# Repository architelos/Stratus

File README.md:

# Stratus

A custom, open source yet practical drone stack.\
Open sourced in the hope that it could serve as a stepping stone in someone else's journey!

## ESC - Jett

**Current revision:** 3\
**Status:** Testing

### Specs

|                    |                                                    |
| ------------------ | -------------------------------------------------- |
| MCU                | STM32G071K(B/8)U(3/6)                              |
| Gate driver        | DRV8300DRGER                                       |
| Input              | 3S to 5S LiPo                                      |
| Continuous current | 25A, 30A peaks                                     |
| Current sensing    | High side hall effect sensor (ACS711)              |
| Firmware           | AM32                                               |

### Description

Built from the ground up to understand what is happening inside an ESC, rather than treating it as a black box. Jett uses industry standard AM32, and has hardware designed around being able to inspect, modify, and learn from the system.

**Power tree:** `VBAT → 10V buck (driving FETs) → 3.3V low-noise LDO`

## Kite (FC)

**Current revision:** 1\
**Status:** Waiting for Jett

### Specs

|                    |                                                    |
| ------------------ | -------------------------------------------------- |
| MCU                | RP2354A                                            |
| IMU                | LSM6DSK320X                                        |
| Input              | 3S to 4S LiPo                                      |
| BECs               | 5V → VTX + Camera; 3V3 → MCU + IMU                 |
| Storage            | MicroSD                                            |
| Firmware           | Betaflight                                         |

The flight controller completes the Stratus stack, with the same focus on practical hardware and understanding the underlying system.

## Acknowledgements <3

Thank you to:
- **AlkaMotors**, **brushlesspower** for the endless patience and willingness to share experience.
- **anticitizen**, **Diamond Master** for design reviews and contributions.

This project would not have been possible without you!

## License

CERN-OHL-S-2.0, see [LICENSE](LICENSE).

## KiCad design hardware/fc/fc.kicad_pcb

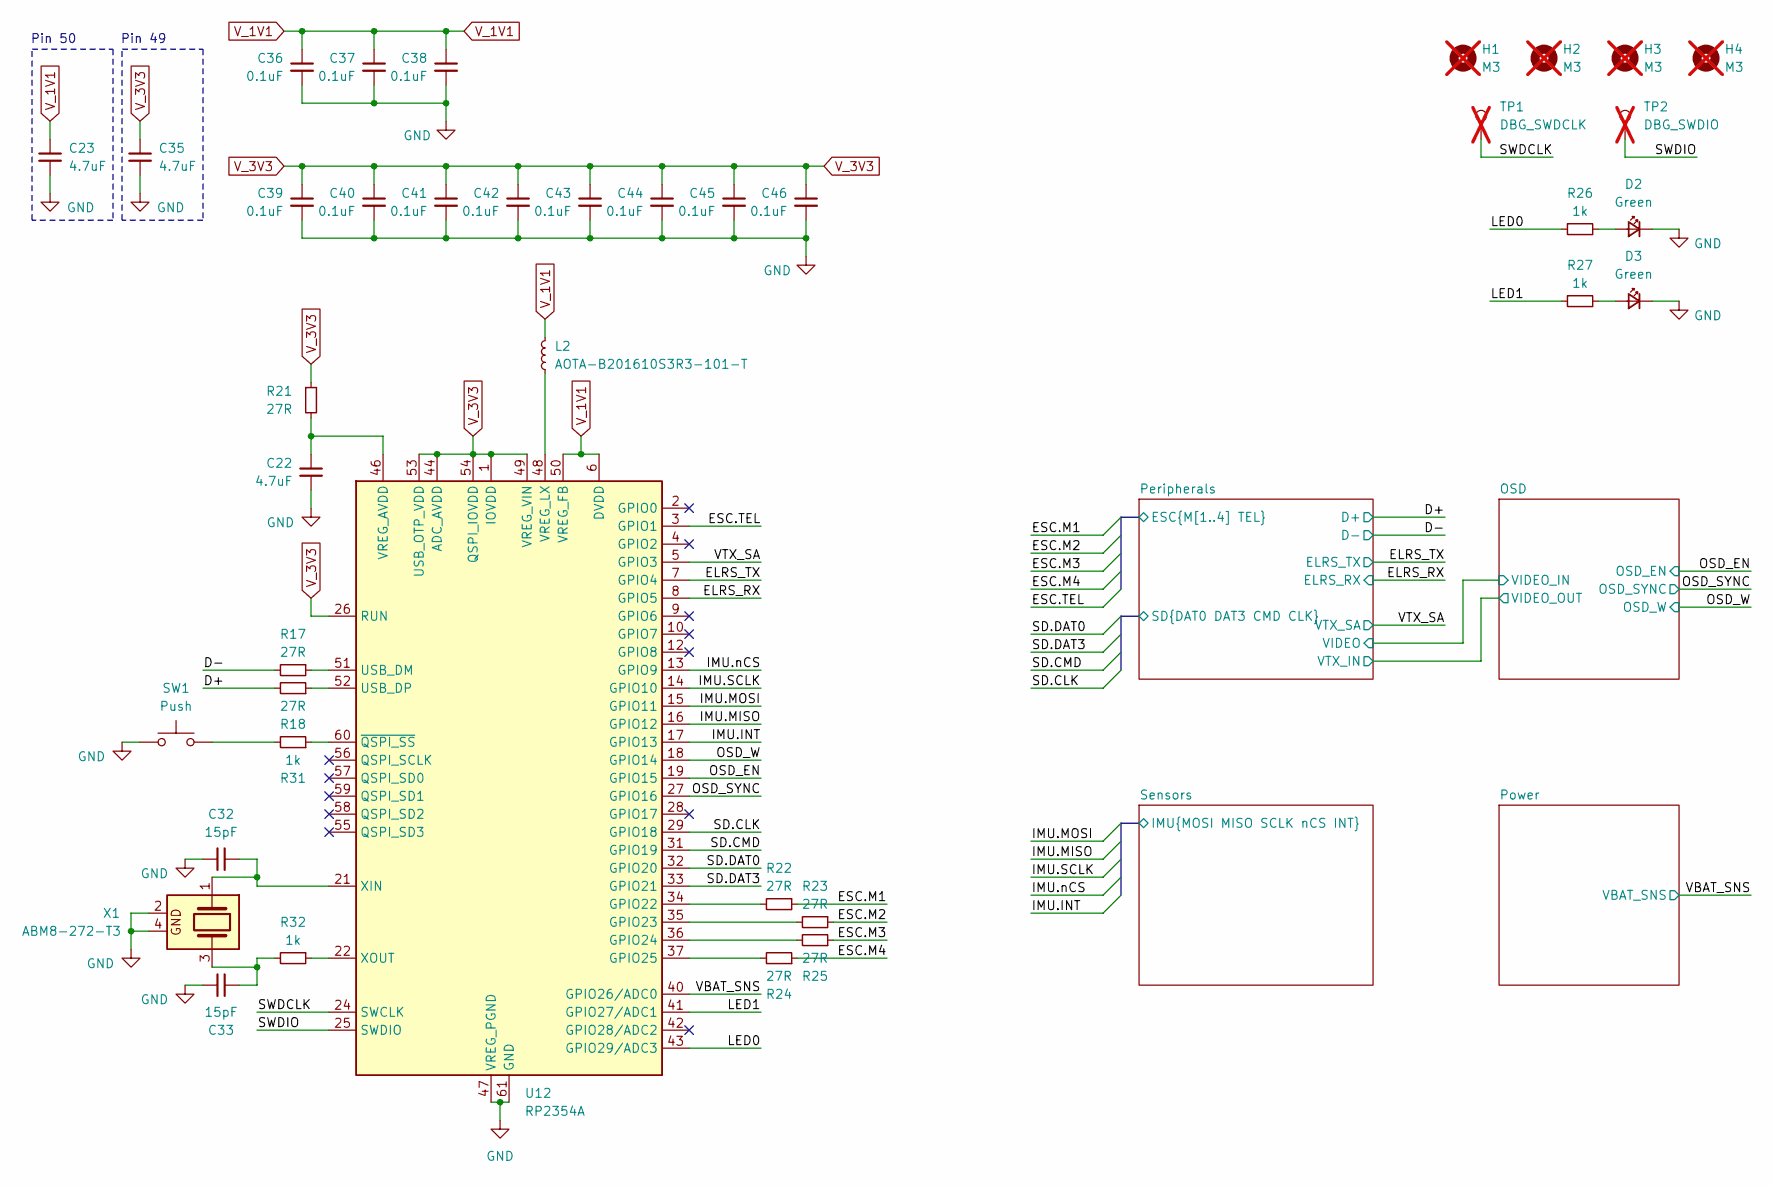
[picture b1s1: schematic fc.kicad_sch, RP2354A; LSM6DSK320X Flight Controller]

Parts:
C22, C23, C35: 4.7uF; C_0402; MPN TDK105CBJ475MV-F; LCSC# C22385335
C32, C33: 15pF; C_0402; MPN CGA2B2C0G1H150JT0Y0F; LCSC# C338103
C36, C37, C38, C39, C40, C41, C42, C43, C44, C45, C46: 0.1uF; C_0402; MPN CGA2B3X7R1V104KT0Y0F; LCSC# C343047
D2, D3: Green; LED_0603_1608Metric; MPN VLMTG1400-GS08; LCSC# C3000897
H1, H2, H3, H4: M3; Mount_M3_K0.5; not fitted
L2: AOTA-B201610S3R3-101-T; L_0806; MPN AOTA-B201610S3R3-101-T; LCSC# C42411119
R17, R18, R21, R22, R23, R24, R25: 27R; R_0402; MPN AC0402FR-0727RL; LCSC# C226392
R26, R27, R31, R32: 1k; R_0402; MPN RC0402FR-071KL; LCSC# C106235
SW1: Push; Push_2x3; MPN EVPAWED40; LCSC# C2858607
TP1: DBG_SWDCLK; Debug_Pad_D1; not fitted
TP2: DBG_SWDIO; Debug_Pad_D1; not fitted
U12: RP2354A; MPN RP2354A; LCSC# C41378174
X1: ABM8-272-T3; Crystal_4P_3.2x2.5mm; MPN ABM8-272-T3; LCSC# C20625731

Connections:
/D+: R18.2; also elsewhere on the board
/D-: R17.2; also elsewhere on the board
/ELRS_RX: U12.8 (GPIO5); also elsewhere on the board
/ELRS_TX: U12.7 (GPIO4); also elsewhere on the board
/LED0: R26.1, U12.43 (GPIO29/ADC3)
/LED1: R27.1, U12.41 (GPIO27/ADC1)
/OSD_EN: U12.19 (GPIO15); also elsewhere on the board
/OSD_SYNC: U12.27 (GPIO16); also elsewhere on the board
/OSD_W: U12.18 (GPIO14); also elsewhere on the board
/Peripherals/ESC.M1: R22.1; also elsewhere on the board
/Peripherals/ESC.M2: R23.1; also elsewhere on the board
/Peripherals/ESC.M3: R25.1; also elsewhere on the board
/Peripherals/ESC.M4: R24.1; also elsewhere on the board
/Peripherals/ESC.TEL: U12.3 (GPIO1); also elsewhere on the board
/Peripherals/SD.CLK: U12.29 (GPIO18); also elsewhere on the board
/Peripherals/SD.CMD: U12.31 (GPIO19); also elsewhere on the board
/Peripherals/SD.DAT0: U12.32 (GPIO20); also elsewhere on the board
/Peripherals/SD.DAT3: U12.33 (GPIO21); also elsewhere on the board
/SWDCLK: TP1.1 (1_1), U12.24 (SWCLK)
/SWDIO: TP2.1 (1_1), U12.25 (SWDIO)
/Sensors/IMU.INT: U12.17 (GPIO13); also elsewhere on the board
/Sensors/IMU.MISO: U12.16 (GPIO12); also elsewhere on the board
/Sensors/IMU.MOSI: U12.15 (GPIO11); also elsewhere on the board
/Sensors/IMU.SCLK: U12.14 (GPIO10); also elsewhere on the board
/Sensors/IMU.nCS: U12.13 (GPIO9); also elsewhere on the board
/VBAT_SNS: U12.40 (GPIO26/ADC0); also elsewhere on the board
/VTX_SA: U12.5 (GPIO3); also elsewhere on the board
GND: C22.2, C23.2, C32.2, C33.2, C35.2, C36.2, C37.2, C38.2, C39.2, C40.2, C41.2, C42.2, C43.2, C44.2, C45.2, C46.2, D2.1 (K), D3.1 (K), SW1.1, U12.47 (VREG_PGND), U12.61 (GND), X1.2, X1.4; also elsewhere on the board
unnamed: C33.1, R32.2, X1.3
unnamed: D2.2 (A), R26.2
unnamed: D3.2 (A), R27.2
unnamed: R31.2, SW1.2
unnamed: R22.2, U12.34 (GPIO22)
unnamed: R23.2, U12.35 (GPIO23)
unnamed: R25.2, U12.36 (GPIO24)
unnamed: R24.2, U12.37 (GPIO25)
unnamed: R17.1, U12.51 (USB_DM)
unnamed: R18.1, U12.52 (USB_DP)
unnamed: C22.1, R21.2, U12.46 (VREG_AVDD)
unnamed: L2.1, U12.48 (VREG_LX)
unnamed: C32.1, U12.21 (XIN), X1.1
unnamed: R32.1, U12.22 (XOUT)
unnamed: R31.1, U12.60 (~QSPI_SS)
V_1V1: C23.1, C36.1, C37.1, C38.1, L2.2, U12.6 (DVDD), U12.23 (DVDD), U12.39 (DVDD), U12.50 (VREG_FB)
V_3V3: C35.1, C39.1, C40.1, C41.1, C42.1, C43.1, C44.1, C45.1, C46.1, R21.1, U12.1 (IOVDD), U12.11 (IOVDD), U12.20 (IOVDD), U12.26 (RUN), U12.30 (IOVDD), U12.38 (IOVDD), U12.44 (ADC_AVDD), U12.45 (IOVDD), U12.49 (VREG_VIN), U12.53 (USB_OTP_VDD), U12.54 (QSPI_IOVDD); also elsewhere on the board

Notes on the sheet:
Pin 50
Pin 49

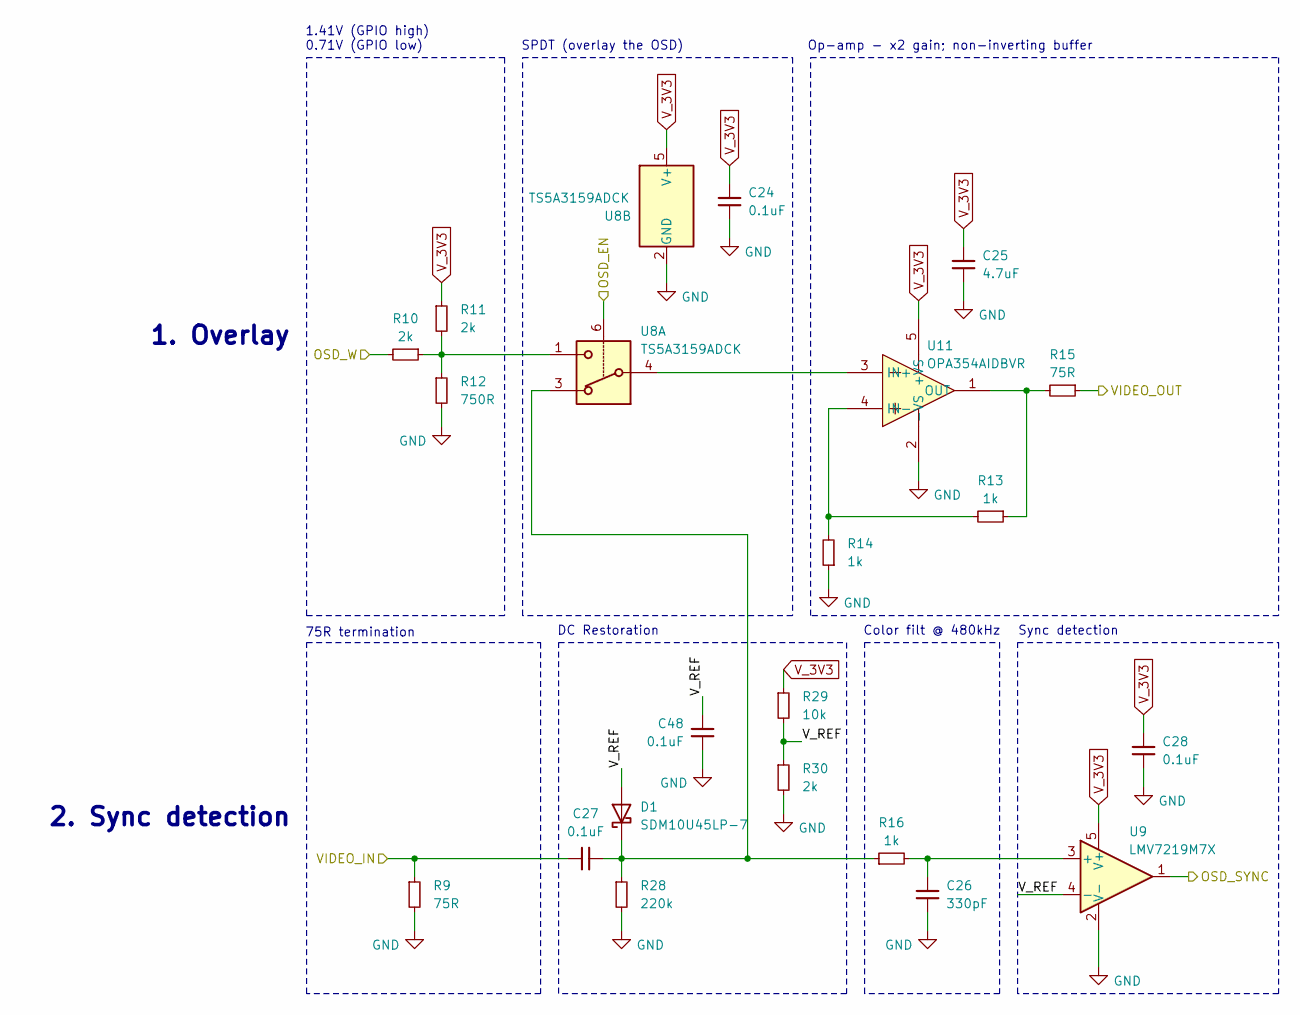
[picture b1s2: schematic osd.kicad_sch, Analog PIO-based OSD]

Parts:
C24, C27, C28, C48: 0.1uF; C_0402; MPN CGA2B3X7R1V104KT0Y0F; LCSC# C343047
C25: 4.7uF; C_0402; MPN TDK105CBJ475MV-F; LCSC# C22385335
C26: 330pF; C_0402; MPN GRM1555C1H331JA01D; LCSC# C76965
D1: SDM10U45LP-7; D_0402; MPN SDM10U45LP-7; LCSC# C78151
R9, R15: 75R; R_0402; MPN RC0402FR-0775RL; LCSC# C114757
R10, R11, R30: 2k; R_0402; MPN RC0402FR-072KL; LCSC# C60488
R12: 750R; R_0402; MPN RC0402FR-07750RL; LCSC# C137936
R13, R14, R16: 1k; R_0402; MPN RC0402FR-071KL; LCSC# C106235
R28: 220k; R_0402; MPN AC0402FR-07220KL; LCSC# C144780
R29: 10k; R_0402; MPN AC0402FR-0710KL; LCSC# C144807
U8: TS5A3159ADCK; MPN TS5A3159ADCK; LCSC# C475493
U9: LMV7219M7X; LMV7219M7X_NOPB; MPN LMV7219M7X; LCSC# C544337
U11: OPA354AIDBVR; MPN OPA354AIDBVR; LCSC# C36384

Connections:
/OSD/VIDEO_IN: C27.2, R9.1; also elsewhere on the board
/OSD/VIDEO_OUT: R15.1; also elsewhere on the board
/OSD/V_REF: C48.2, D1.2 (A), R29.2, R30.1, U9.4 (-)
/OSD_EN: U8.6; also elsewhere on the board
/OSD_SYNC: U9.1; also elsewhere on the board
/OSD_W: R10.2; also elsewhere on the board
GND: C24.2, C25.2, C26.2, C28.2, C48.1, R9.2, R12.2, R14.1, R28.2, R30.2, U8.2 (GND), U9.2 (V-), U11.2 (-VS); also elsewhere on the board
unnamed: C27.1, D1.1 (K), R16.1, R28.1, U8.3
unnamed: R10.1, R11.2, R12.1, U8.1
unnamed: C26.1, R16.2, U9.3 (+)
unnamed: U8.4, U11.3 (IN+)
unnamed: R13.2, R14.2, U11.4 (IN-)
unnamed: R13.1, R15.2, U11.1 (OUT)
V_3V3: C24.1, C25.1, C28.1, R11.1, R29.1, U8.5 (V+), U9.5 (V+), U11.5 (+VS); also elsewhere on the board

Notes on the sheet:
75R termination
Op-amp - x2 gain; non-inverting buffer
2. Sync detection
1.41V (GPIO high) 0.71V (GPIO low)
Color filt @ 480kHz
Sync detection
DC Restoration
SPDT (overlay the OSD)
1. Overlay

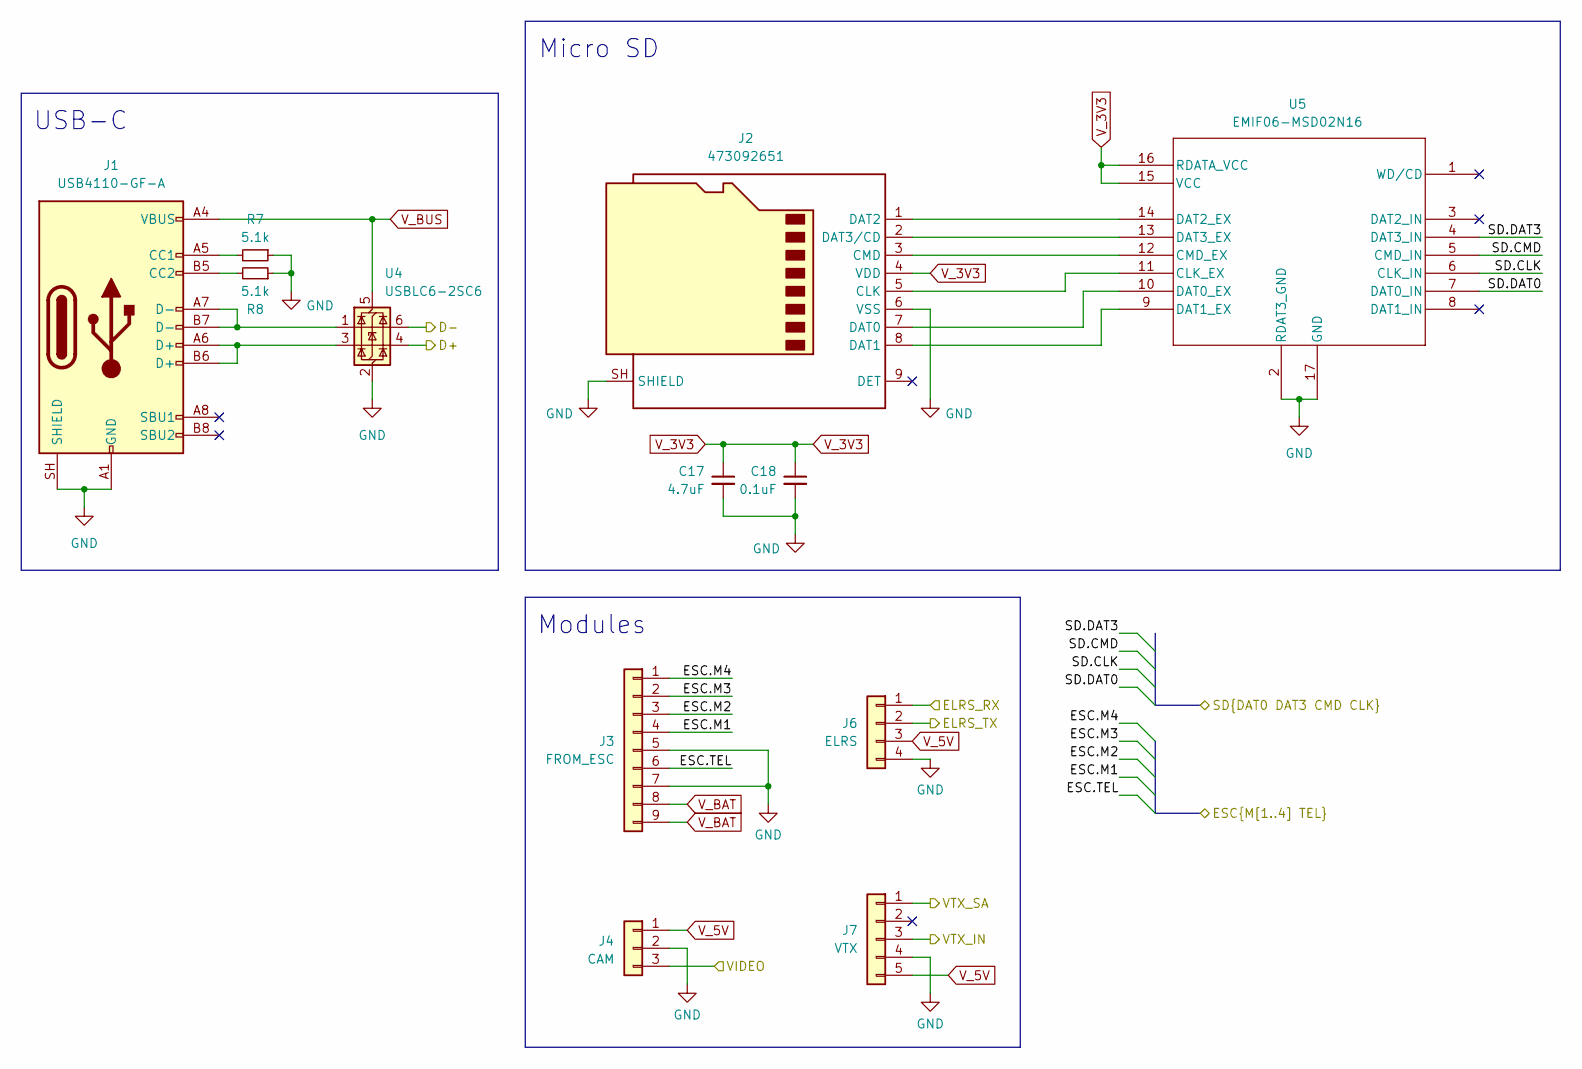
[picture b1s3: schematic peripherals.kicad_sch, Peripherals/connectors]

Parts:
C17: 4.7uF; C_0402; MPN TDK105CBJ475MV-F; LCSC# C22385335
C18: 0.1uF; C_0402; MPN CGA2B3X7R1V104KT0Y0F; LCSC# C343047
J1: USB4110-GF-A; USB_C_Receptacle_GCT_USB4110; MPN USB4110-GF-A; LCSC# C5143397
J2: 473092651; 0473092651; MPN 473092651; LCSC# C587826
J3: FROM_ESC; JST_SH_SM09B-SRSS-TB_1x09-1MP_P1.00mm_Horizontal; MPN SM09B-SRSS-TB(LF)(SN); LCSC# C160408
J4: CAM; JST_SH_SM03B-SRSS-TB_1x03-1MP_P1.00mm_Horizontal; MPN SM03B-SRSS-TB(LF)(SN); LCSC# C160403
J6: ELRS; JST_SH_SM04B-SRSS-TB_1x04-1MP_P1.00mm_Horizontal; MPN SM04B-SRSS-TB(LF)(SN); LCSC# C160404
J7: VTX; JST_SH_SM05B-SRSS-TB_1x05-1MP_P1.00mm_Horizontal; MPN SM05B-SRSS-TB(LF)(SN); LCSC# C136657
R7, R8: 5.1k; R_0402; MPN RC0402FR-075K1L; LCSC# C105872
U4: USBLC6-2SC6; MPN USBLC6-2SC6; LCSC# C7519
U5: EMIF06-MSD02N16; MPN EMIF06-MSD02N16; LCSC# C5267594

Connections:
/D+: U4.4 (I/O2); also elsewhere on the board
/D-: U4.6 (I/O1); also elsewhere on the board
/ELRS_RX: J6.1; also elsewhere on the board
/ELRS_TX: J6.2; also elsewhere on the board
/OSD/VIDEO_IN: J4.3; also elsewhere on the board
/OSD/VIDEO_OUT: J7.3; also elsewhere on the board
/Peripherals/ESC.M1: J3.4; also elsewhere on the board
/Peripherals/ESC.M2: J3.3; also elsewhere on the board
/Peripherals/ESC.M3: J3.2; also elsewhere on the board
/Peripherals/ESC.M4: J3.1; also elsewhere on the board
/Peripherals/ESC.TEL: J3.6; also elsewhere on the board
/Peripherals/SD.CLK: U5.6 (CLK_IN); also elsewhere on the board
/Peripherals/SD.CMD: U5.5 (CMD_IN); also elsewhere on the board
/Peripherals/SD.DAT0: U5.7 (DAT0_IN); also elsewhere on the board
/Peripherals/SD.DAT3: U5.4 (DAT3_IN); also elsewhere on the board
/VTX_SA: J7.1; also elsewhere on the board
GND: C17.2, C18.2, J1.A1 (GND), J1.A12 (GND), J1.B1 (GND), J1.B12 (GND), J1.SH (SHIELD), J2.6 (VSS), J2.SH (SHIELD), J3.5, J3.7, J4.2, J6.4, J7.4, R7.1, R8.1, U4.2 (GND), U5.2 (RDAT3_GND), U5.17 (GND); also elsewhere on the board
unnamed: J1.A5 (CC1), R7.2
unnamed: J1.B5 (CC2), R8.2
unnamed: J1.A6 (D+), J1.B6 (D+), U4.3 (I/O2)
unnamed: J1.A7 (D-), J1.B7 (D-), U4.1 (I/O1)
unnamed: J2.5 (CLK), U5.11 (CLK_EX)
unnamed: J2.3 (CMD), U5.12 (CMD_EX)
unnamed: J2.7 (DAT0), U5.10 (DAT0_EX)
unnamed: J2.8 (DAT1), U5.9 (DAT1_EX)
unnamed: J2.1 (DAT2), U5.14 (DAT2_EX)
unnamed: J2.2 (DAT3/CD), U5.13 (DAT3_EX)
V_3V3: C17.1, C18.1, J2.4 (VDD), U5.15 (VCC), U5.16 (RDATA_VCC); also elsewhere on the board
V_5V: J4.1, J6.3, J7.5; also elsewhere on the board
V_BAT: J3.8, J3.9; also elsewhere on the board
V_BUS: J1.A4 (VBUS), J1.A9 (VBUS), J1.B4 (VBUS), J1.B9 (VBUS), U4.5 (VBUS); also elsewhere on the board

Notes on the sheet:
USB-C
Micro SD
Modules

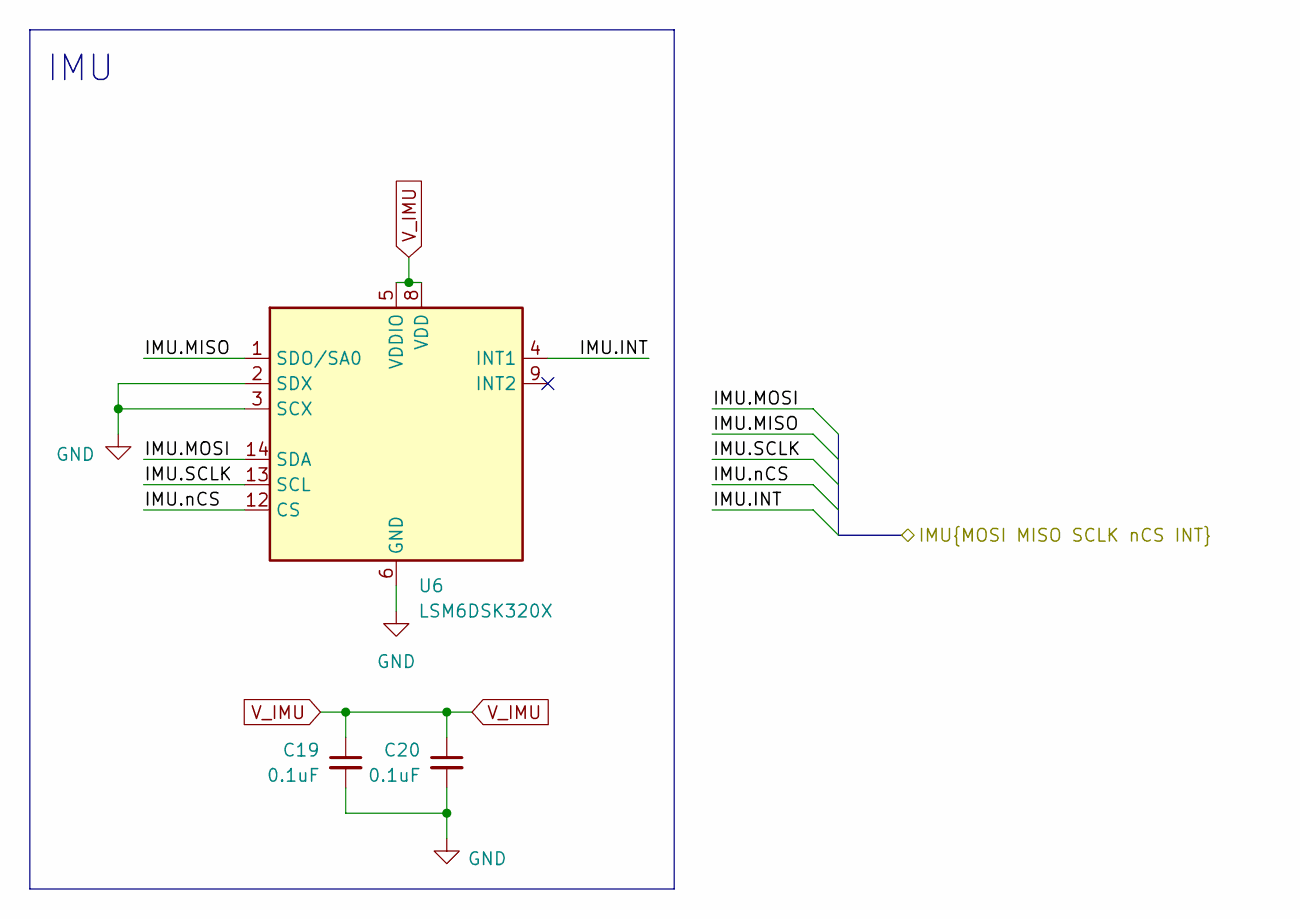
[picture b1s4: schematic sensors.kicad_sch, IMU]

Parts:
C19, C20: 0.1uF; C_0402; MPN CGA2B3X7R1V104KT0Y0F; LCSC# C343047
U6: LSM6DSK320X; MPN LSM6DSK320XTR; LCSC# C53025794

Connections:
/Sensors/IMU.INT: U6.4 (INT1); also elsewhere on the board
/Sensors/IMU.MISO: U6.1 (SDO/SA0); also elsewhere on the board
/Sensors/IMU.MOSI: U6.14 (SDA); also elsewhere on the board
/Sensors/IMU.SCLK: U6.13 (SCL); also elsewhere on the board
/Sensors/IMU.nCS: U6.12 (CS); also elsewhere on the board
GND: C19.2, C20.2, U6.2 (SDX), U6.3 (SCX), U6.6 (GND), U6.7 (GND); also elsewhere on the board
V_IMU: C19.1, C20.1, U6.5 (VDDIO), U6.8 (VDD); also elsewhere on the board

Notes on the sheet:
IMU

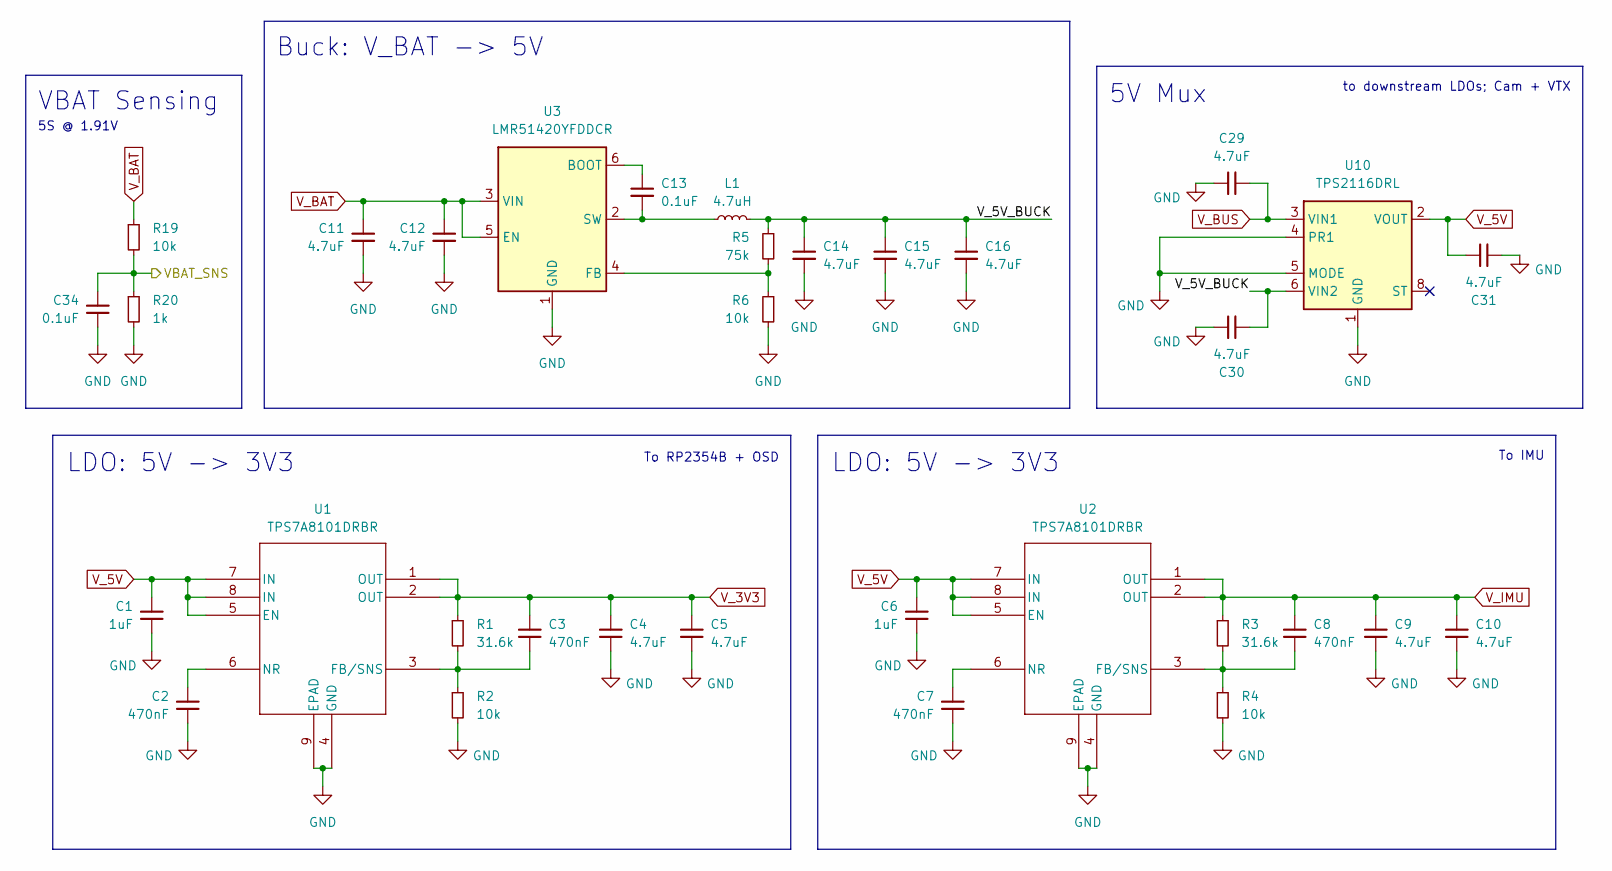
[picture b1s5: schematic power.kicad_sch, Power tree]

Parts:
C1, C6: 1uF; C_0402; MPN GRM155R6YA105KE11J; LCSC# C3835721
C2, C3, C7, C8: 470nF; C_0402; MPN CL05A474KA5NNNC; LCSC# C92361
C4, C5, C9, C10, C14, C15, C16, C29, C30, C31: 4.7uF; C_0402; MPN TDK105CBJ475MV-F; LCSC# C22385335
C11, C12: 4.7uF; C_0603_1608Metric; MPN CL10A475KL8NRNC; LCSC# C307467
C13, C34: 0.1uF; C_0402; MPN CGA2B3X7R1V104KT0Y0F; LCSC# C343047
L1: 4.7uH; L_1210_3225Metric; MPN BCL322520RT-4R7M-D; LCSC# C3224690
R1, R3: 31.6k; R_0402; MPN AC0402FR-0731K6L; LCSC# C226989
R2, R4, R6, R19: 10k; R_0402; MPN AC0402FR-0710KL; LCSC# C144807
R5: 75k; R_0402; MPN RC0402FR-0775KL; LCSC# C137935
R20: 1k; R_0402; MPN RC0402FR-071KL; LCSC# C106235
U1, U2: TPS7A8101DRBR; MPN TPS7A8101DRBR; LCSC# C465730
U3: LMR51420YFDDCR; MPN LMR51420YFDDCR; LCSC# C7296200
U10: TPS2116DRL; MPN TPS2116DRLR; LCSC# C3235557

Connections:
/Power/V_5V_BUCK: C14.1, C15.1, C16.1, C30.1, L1.2, R5.1, U10.6 (VIN2)
/VBAT_SNS: C34.1, R19.2, R20.1; also elsewhere on the board
GND: C1.2, C2.2, C4.2, C5.2, C6.2, C7.2, C9.2, C10.2, C11.2, C12.2, C14.2, C15.2, C16.2, C29.2, C30.2, C31.2, C34.2, R2.2, R4.2, R6.2, R20.2, U1.4 (GND), U1.9 (EPAD), U2.4 (GND), U2.9 (EPAD), U3.1 (GND), U10.1 (GND), U10.4 (PR1), U10.5 (MODE); also elsewhere on the board
unnamed: C3.2, R1.2, R2.1, U1.3 (FB/SNS)
unnamed: C2.1, U1.6 (NR)
unnamed: C8.2, R3.2, R4.1, U2.3 (FB/SNS)
unnamed: C7.1, U2.6 (NR)
unnamed: C13.1, U3.6 (BOOT)
unnamed: R5.2, R6.1, U3.4 (FB)
unnamed: C13.2, L1.1, U3.2 (SW)
V_3V3: C3.1, C4.1, C5.1, R1.1, U1.1 (OUT), U1.2 (OUT); also elsewhere on the board
V_5V: C1.1, C6.1, C31.1, U1.5 (EN), U1.7 (IN), U1.8 (IN), U2.5 (EN), U2.7 (IN), U2.8 (IN), U10.2 (VOUT), U10.7 (VOUT); also elsewhere on the board
V_BAT: C11.1, C12.1, R19.1, U3.3 (VIN), U3.5 (EN); also elsewhere on the board
V_BUS: C29.1, U10.3 (VIN1); also elsewhere on the board
V_IMU: C8.1, C9.1, C10.1, R3.1, U2.1 (OUT), U2.2 (OUT); also elsewhere on the board

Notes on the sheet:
VBAT Sensing
To RP2354B + OSD
LDO: 5V -> 3V3
5V Mux
To IMU
Buck: V_BAT -> 5V
5S @ 1.91V
to downstream LDOs; Cam + VTX

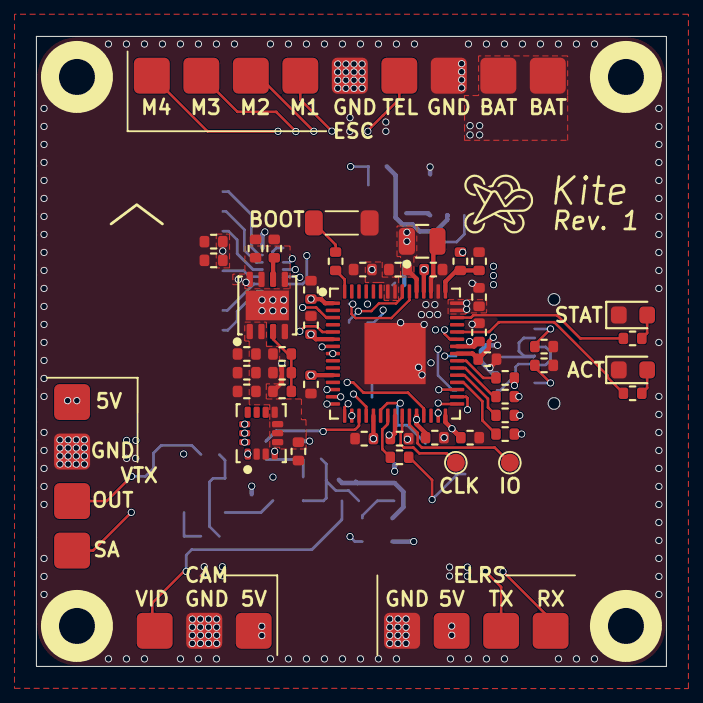
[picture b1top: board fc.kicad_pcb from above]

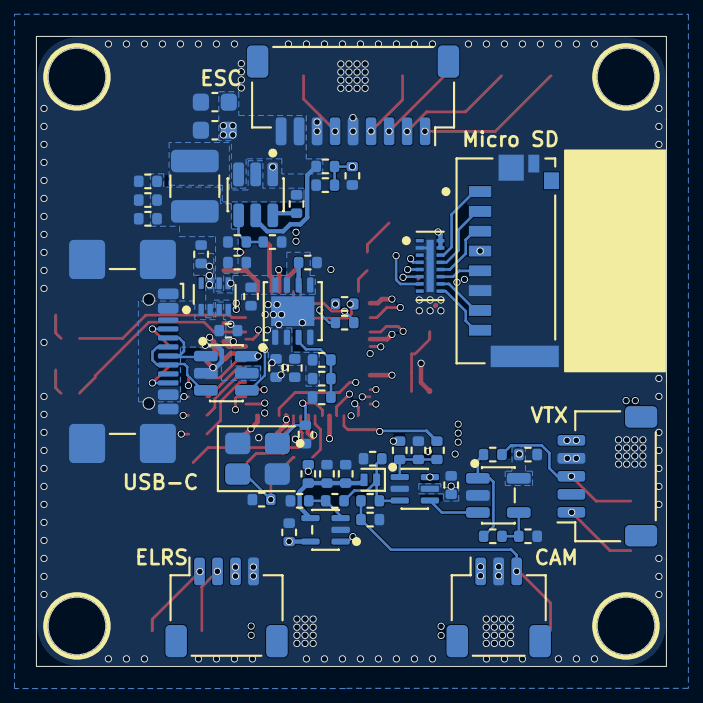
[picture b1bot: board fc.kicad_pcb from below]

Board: 6 copper layers, 35.0 x 35.0 mm, 108 parts (59 on the bottom side), 76 nets.

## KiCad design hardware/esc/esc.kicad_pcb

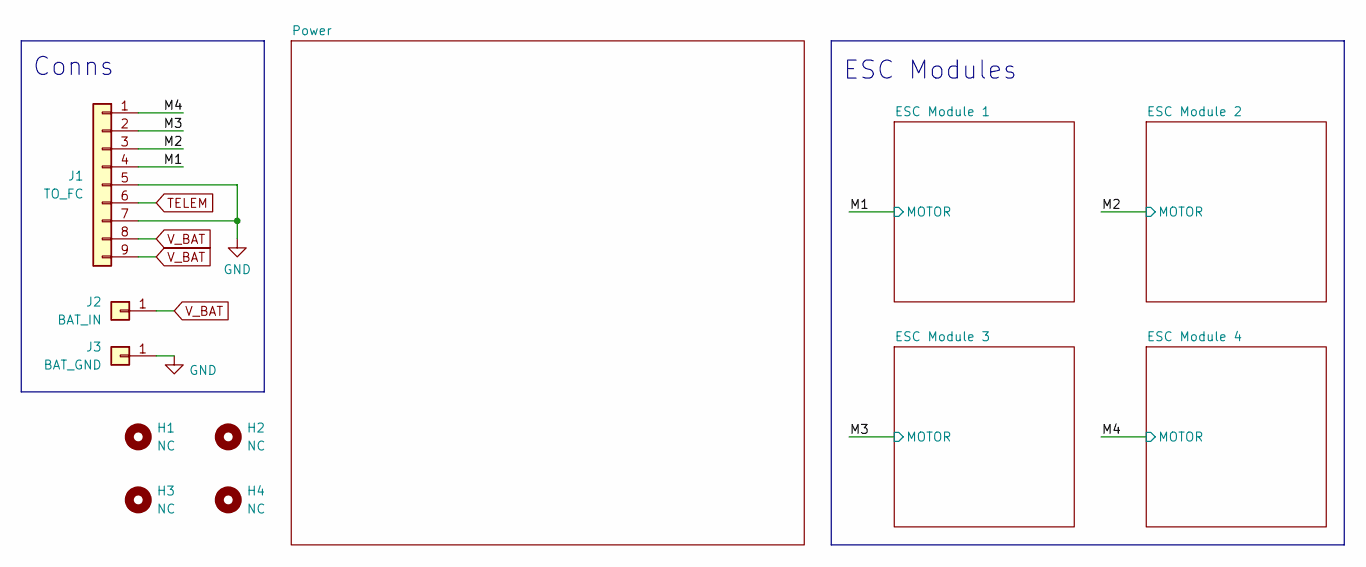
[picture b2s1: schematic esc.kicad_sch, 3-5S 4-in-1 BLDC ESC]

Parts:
H1, H2, H3, H4: NC; Mount_M3_K0.5
J1: TO_FC; JST_SH_1x9_ESC; MPN SM09B-SRSS-TB(LF)(SN); LCSC# C160408
J2: BAT_IN; Input_5x5_D2.5_R
J3: BAT_GND; Input_5x5_D2.5_L

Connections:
/M1: J1.4; also elsewhere on the board
/M2: J1.3; also elsewhere on the board
/M3: J1.2; also elsewhere on the board
/M4: J1.1; also elsewhere on the board
GND: J1.5, J1.7, J3.1 (Pin_1_1); also elsewhere on the board
TELEM: J1.6; also elsewhere on the board
V_BAT: J1.8, J1.9, J2.1 (Pin_1_1); also elsewhere on the board

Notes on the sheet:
ESC Modules
Conns
